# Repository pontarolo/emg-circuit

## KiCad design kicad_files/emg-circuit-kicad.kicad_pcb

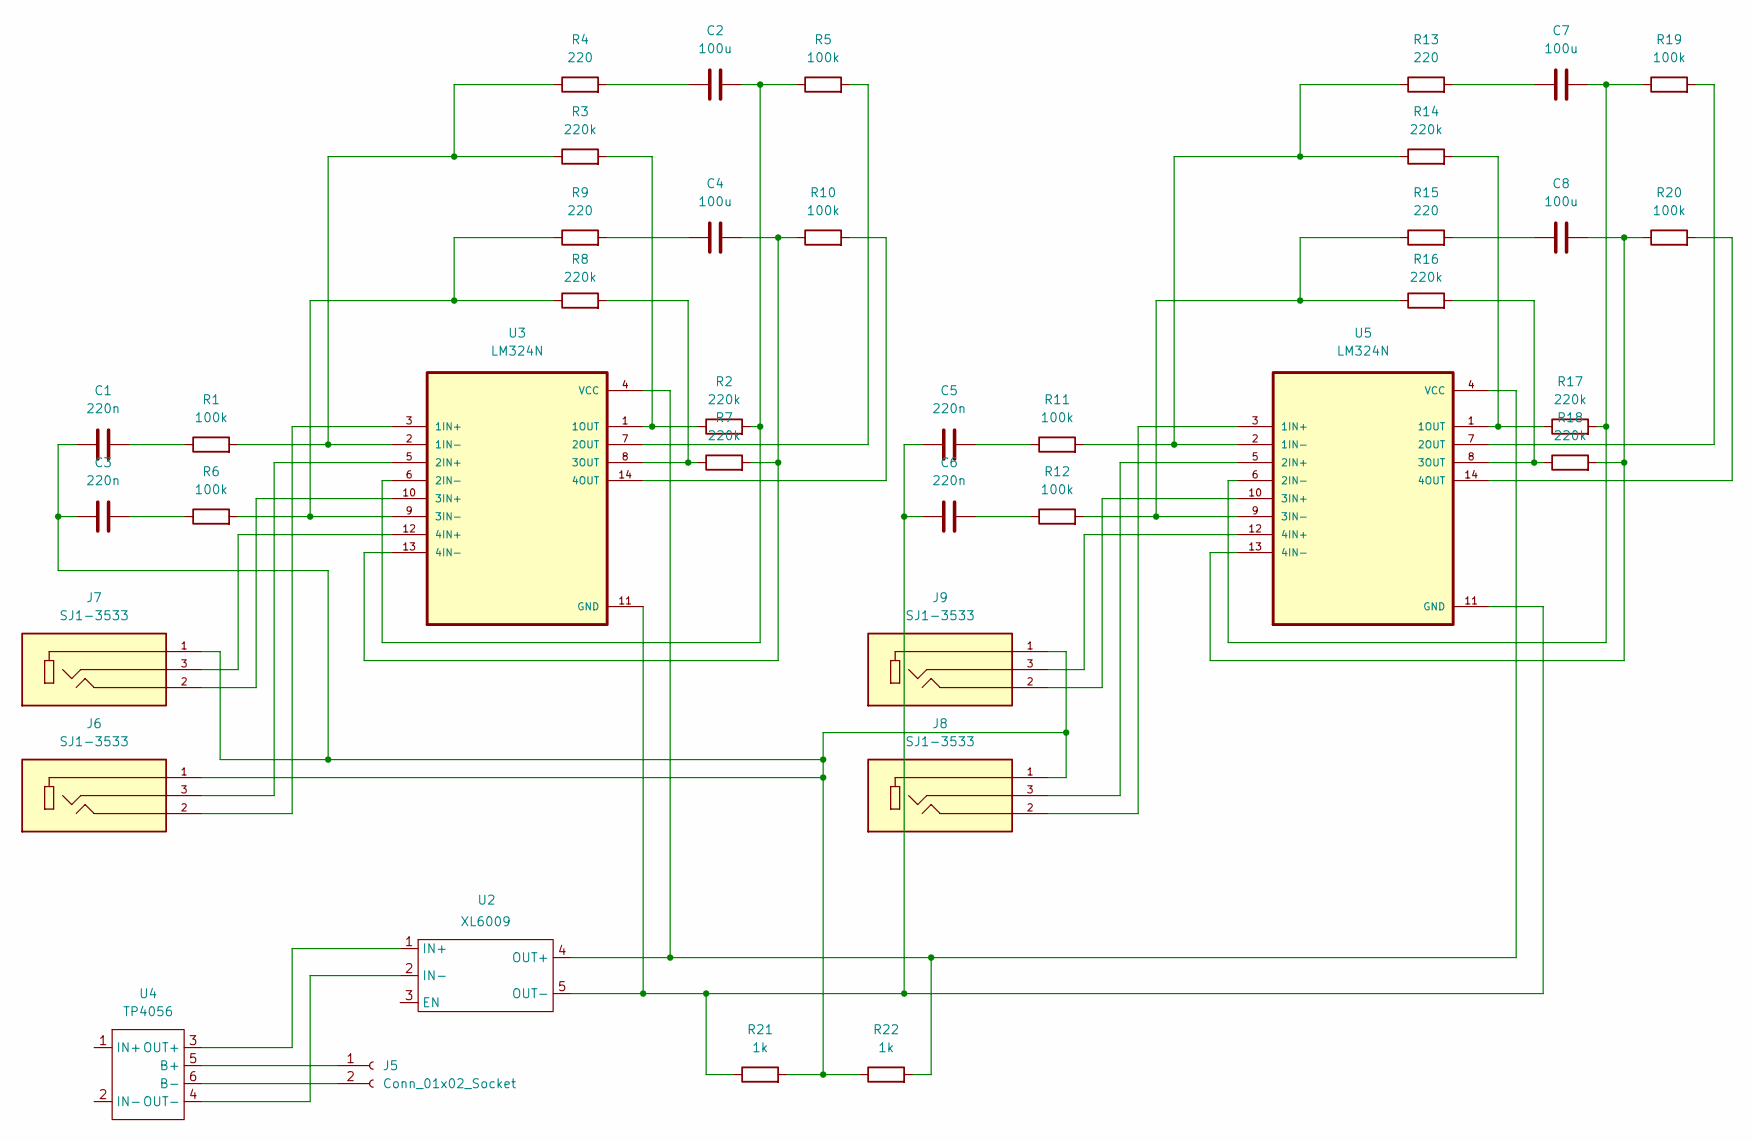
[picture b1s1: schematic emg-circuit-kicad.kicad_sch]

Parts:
C1, C3, C5, C6: 220n; CP_Radial_D6.3mm_P2.50mm
C2, C4, C7, C8: 100u; CP_Radial_D6.3mm_P2.50mm
J5: Conn_01x02_Socket
J6, J7, J8, J9: SJ1-3533; CUI_SJ1-3533; PARTREV 1.01
R1, R5, R6, R10, R11, R12, R19, R20: 100k; R_Axial_DIN0207_L6.3mm_D2.5mm_P10.16mm_Horizontal
R2, R3, R7, R8, R14, R16, R17, R18: 220k; R_Axial_DIN0207_L6.3mm_D2.5mm_P10.16mm_Horizontal
R4, R9, R13, R15: 220; R_Axial_DIN0207_L6.3mm_D2.5mm_P10.16mm_Horizontal
R21, R22: 1k; R_Axial_DIN0207_L6.3mm_D2.5mm_P10.16mm_Horizontal
U2: XL6009; XL6009_Module
U3, U5: LM324N; DIP794W45P254L1969H508Q14
U4: TP4056; TP4056-Module

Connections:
unnamed: C1.1, C3.1, J6.1, J7.1, J8.1, J9.1, R21.2, R22.1
unnamed: C1.2, R1.1
unnamed: C2.1, R4.2
unnamed: C3.2, R6.1
unnamed: C4.1, R9.2
unnamed: C5.2, R11.1
unnamed: C6.2, R12.1
unnamed: C7.1, R13.2
unnamed: C8.1, R15.2
unnamed: J5.1, U4.5 (B+)
unnamed: J5.2, U4.6 (B-)
unnamed: U2.1 (IN+), U4.3 (OUT+)
unnamed: U2.2 (IN-), U4.4 (OUT-)
unnamed: R22.2, U2.4 (OUT+), U3.4 (VCC), U5.4 (VCC)
unnamed: C5.1, C6.1, R21.1, U2.5 (OUT-), U3.11 (GND), U5.11 (GND)
unnamed: J6.2, U3.3 (1IN+)
unnamed: R1.2, R3.1, R4.1, U3.2 (1IN-)
unnamed: R2.1, R3.2, U3.1 (1OUT)
unnamed: J6.3, U3.5 (2IN+)
unnamed: C2.2, R2.2, R5.1, U3.6 (2IN-)
unnamed: R5.2, U3.7 (2OUT)
unnamed: J7.2, U3.10 (3IN+)
unnamed: R6.2, R8.1, R9.1, U3.9 (3IN-)
unnamed: R7.1, R8.2, U3.8 (3OUT)
unnamed: J7.3, U3.12 (4IN+)
unnamed: C4.2, R7.2, R10.1, U3.13 (4IN-)
unnamed: R10.2, U3.14 (4OUT)
unnamed: J8.2, U5.3 (1IN+)
unnamed: R11.2, R13.1, R14.1, U5.2 (1IN-)
unnamed: R14.2, R17.1, U5.1 (1OUT)
unnamed: J8.3, U5.5 (2IN+)
unnamed: C7.2, R17.2, R19.1, U5.6 (2IN-)
unnamed: R19.2, U5.7 (2OUT)
unnamed: J9.2, U5.10 (3IN+)
unnamed: R12.2, R15.1, R16.1, U5.9 (3IN-)
unnamed: R16.2, R18.1, U5.8 (3OUT)
unnamed: J9.3, U5.12 (4IN+)
unnamed: C8.2, R18.2, R20.1, U5.13 (4IN-)
unnamed: R20.2, U5.14 (4OUT)

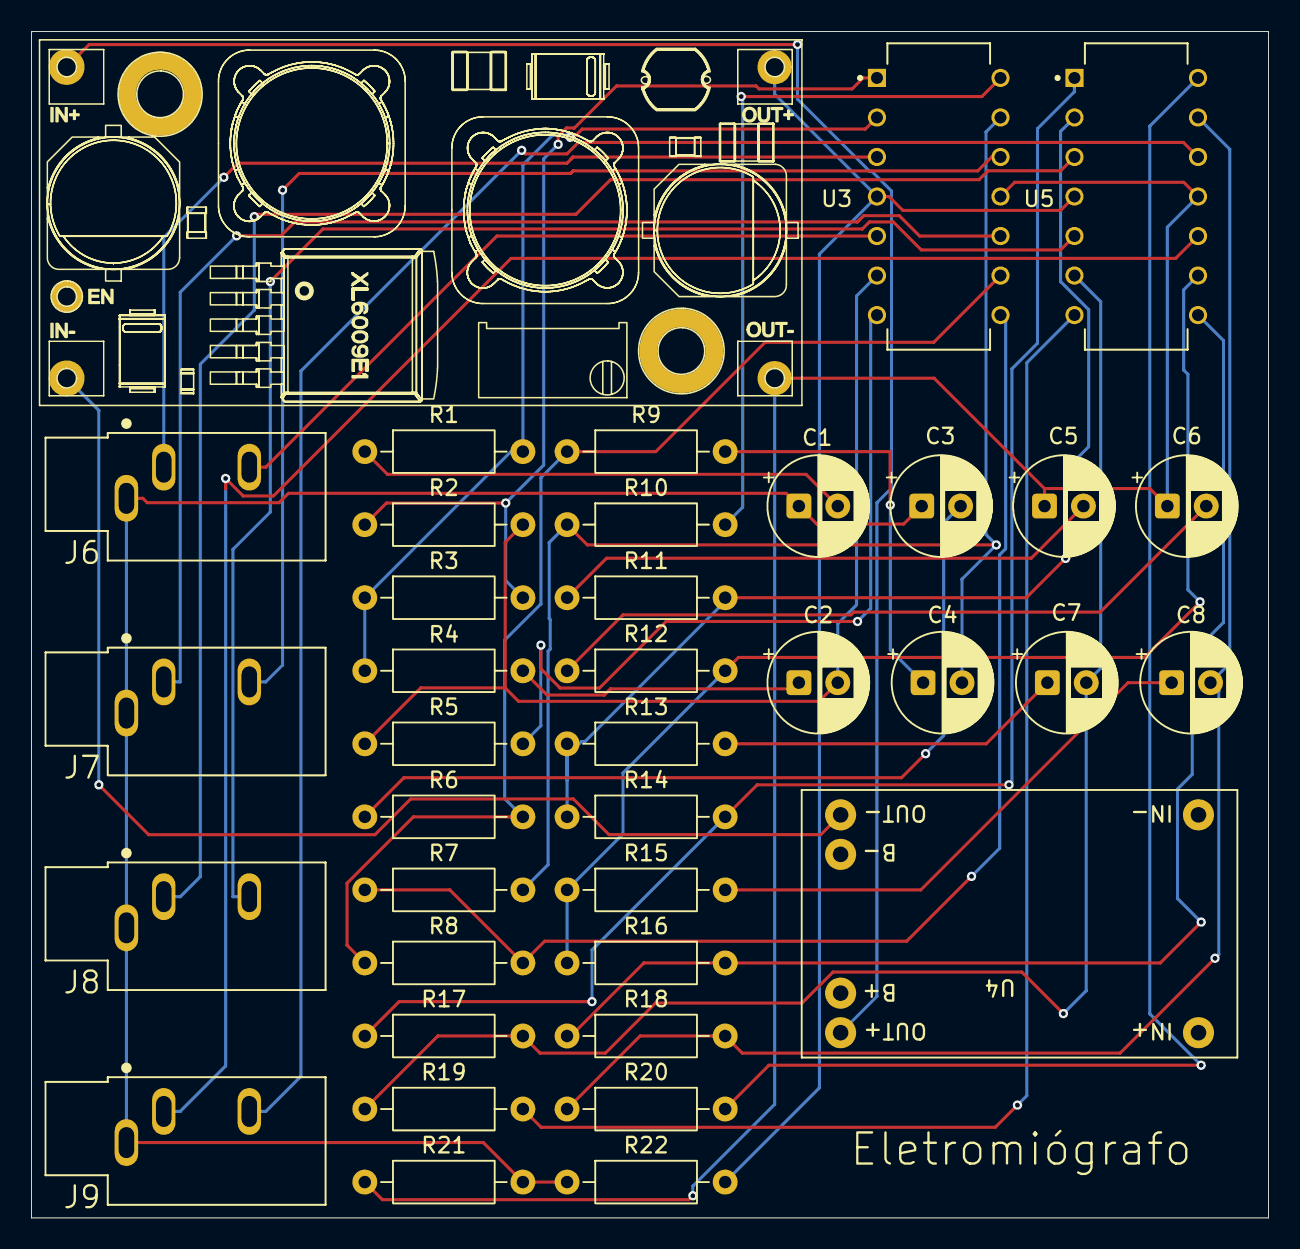
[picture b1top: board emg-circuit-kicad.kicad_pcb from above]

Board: 2 copper layers, 79.5 x 76.2 mm, 38 parts (0 on the bottom side), 37 nets.

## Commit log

2026-04-20 feat: first commit
2026-04-20 fix: update footprints
2026-04-22 fix: move component label into the pcb area
